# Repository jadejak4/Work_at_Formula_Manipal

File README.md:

# Work at Formula Manipal

Hi, hope this finds you well. This repository summarizes the majority of the technical work that was executed collaboratively by my teammates and me during my tenure at Formula Manipal.

## Projects at Formula Manipal

Broadly speaking, my projects at FM included:

- **Hardware & Firmware Design** of a Data Acquisition system for a Formula Student car.
- **Integrating a telemetry system** using XBee modules & displaying data using a GUI.
- **Designing & manufacturing a wiring harness**, compatible with the mechanical design and Engine Control Unit.
- **Designing, prototyping & manufacturing PCBs** for digital circuits used in the shutdown system for the car.

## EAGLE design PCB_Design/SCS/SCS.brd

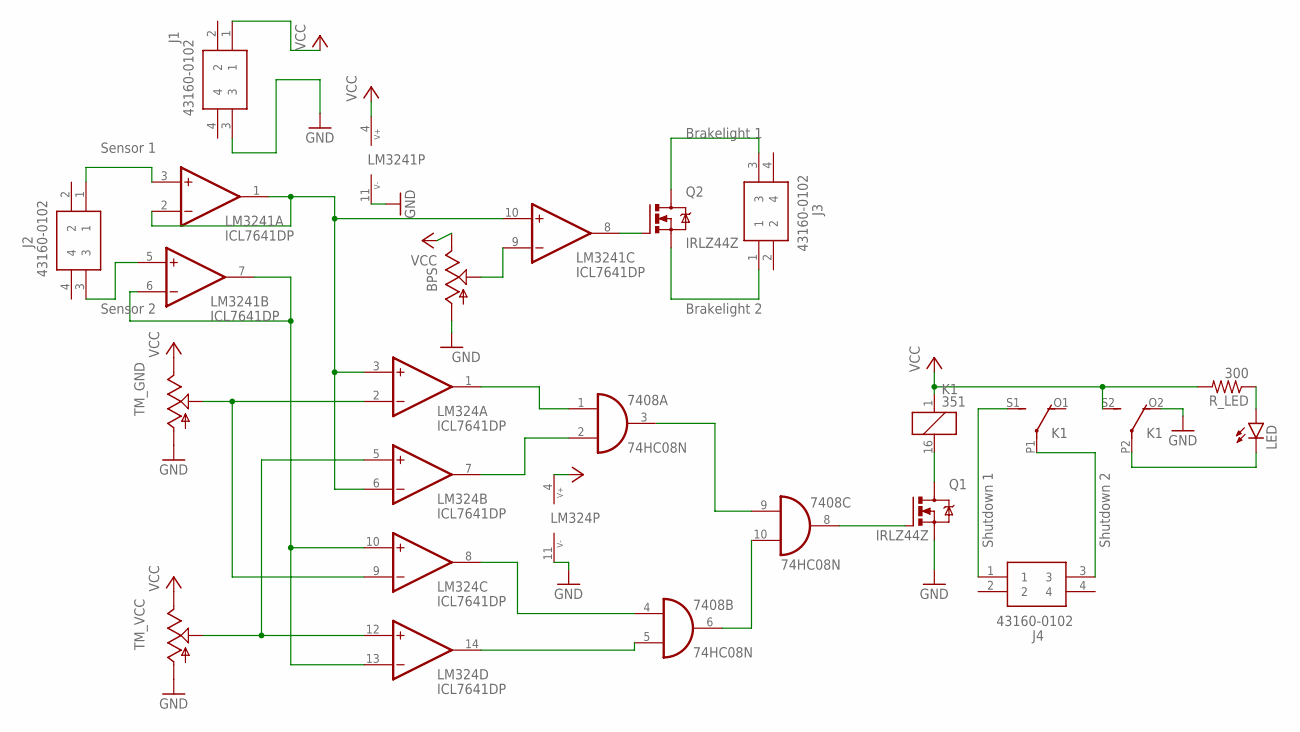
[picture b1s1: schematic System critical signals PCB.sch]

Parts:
7408: 74HC08N; DIL14
BPS: TRIM; 6MM
J1, J2, J3, J4: 43160-0102; 431600102
K1: 351
LED: LEDCHIP-LED0805; CHIP-LED0805
LM324, LM3241: ICL7641DP; DIL14
Q1, Q2: IRLZ44Z; TO220BH
R_LED: 300; M0805
TM_GND: TRIM; 6MM
TM_VCC: TRIM; 6MM

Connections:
GND: 7408.7 (GND), BPS.A, J1.3, K1.O2 (O), LM324.11 (V-), LM3241.11 (V-), Q1.S, TM_GND.A, TM_VCC.A
unnamed: 7408.4 (I0), LM324.8 (OUT)
unnamed: LM324.3 (+IN), LM324.6 (-IN), LM3241.1 (OUT), LM3241.2 (-IN), LM3241.10 (+IN)
unnamed: LM324.10 (+IN), LM324.13 (-IN), LM3241.6 (-IN), LM3241.7 (OUT)
unnamed: 7408.5 (I1), LM324.14 (OUT)
unnamed: 7408.1 (I0), LM324.1 (OUT)
unnamed: 7408.2 (I1), LM324.7 (OUT)
unnamed: 7408.3 (O), 7408.9 (I0)
unnamed: 7408.6 (O), 7408.10 (I1)
unnamed: 7408.8 (O), Q1.G
unnamed: K1.16 (2), Q1.D
unnamed: J4.1, K1.S1 (S)
unnamed: J4.3, K1.P1
unnamed: LED.A, R_LED.1
unnamed: BPS.S, LM3241.9 (-IN)
unnamed: LM3241.8 (OUT), Q2.G
unnamed: J3.3, Q2.D
unnamed: J3.1, Q2.S
unnamed: K1.P2, LED.C
unnamed: J2.1, LM3241.3 (+IN)
unnamed: J2.3, LM3241.5 (+IN)
unnamed: LM324.2 (-IN), LM324.9 (-IN), TM_GND.S
unnamed: LM324.5 (+IN), LM324.12 (+IN), TM_VCC.S
VCC: 7408.14 (VCC), BPS.E, J1.1, K1.1, K1.S2 (S), LM324.4 (V+), LM3241.4 (V+), R_LED.2, TM_GND.E, TM_VCC.E

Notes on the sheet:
Sensor 1
Sensor 2
Shutdown 1
Shutdown 2
Brakelight 1
Brakelight 2

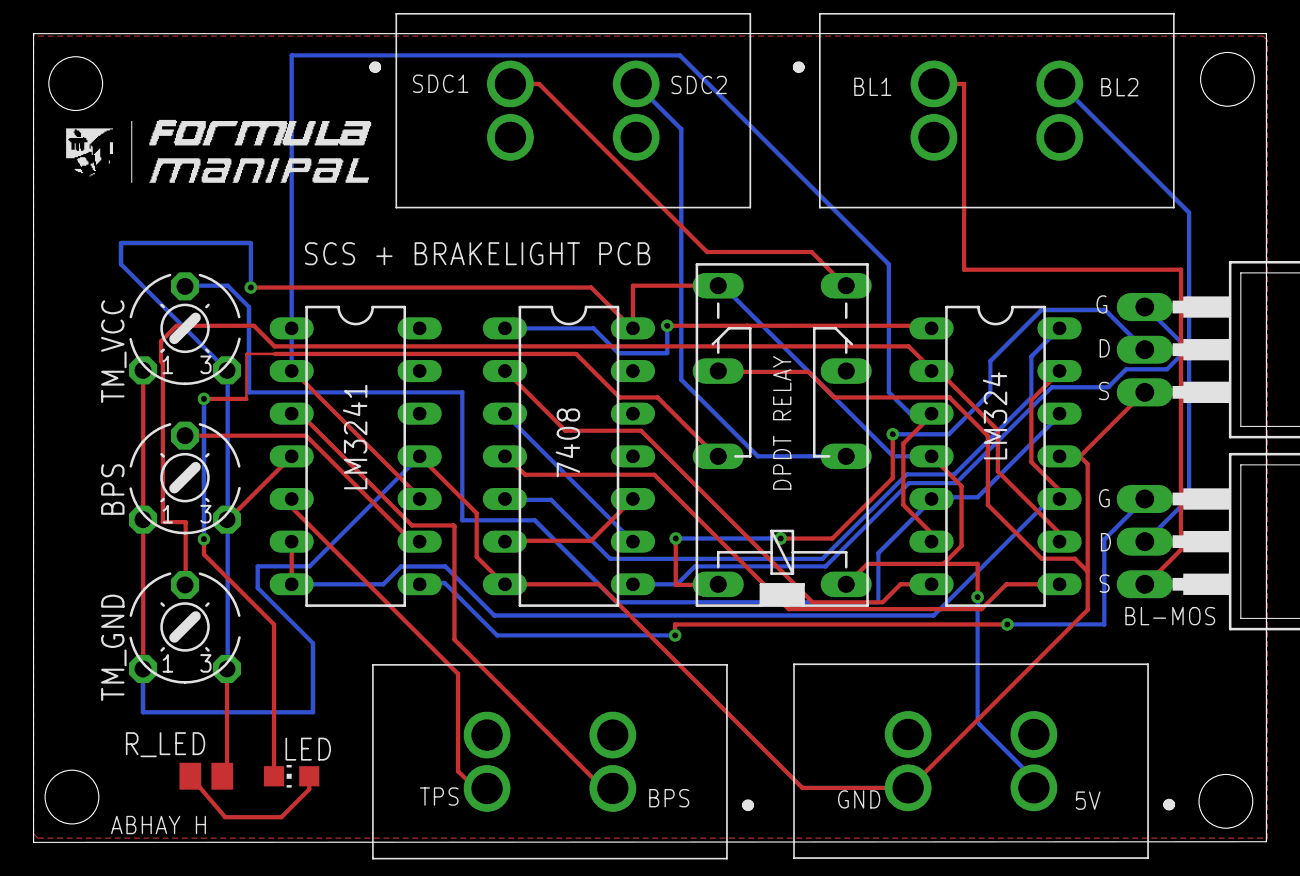
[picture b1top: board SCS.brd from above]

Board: 2 copper layers, 73.4 x 48.2 mm, 15 parts (0 on the bottom side), 24 nets.

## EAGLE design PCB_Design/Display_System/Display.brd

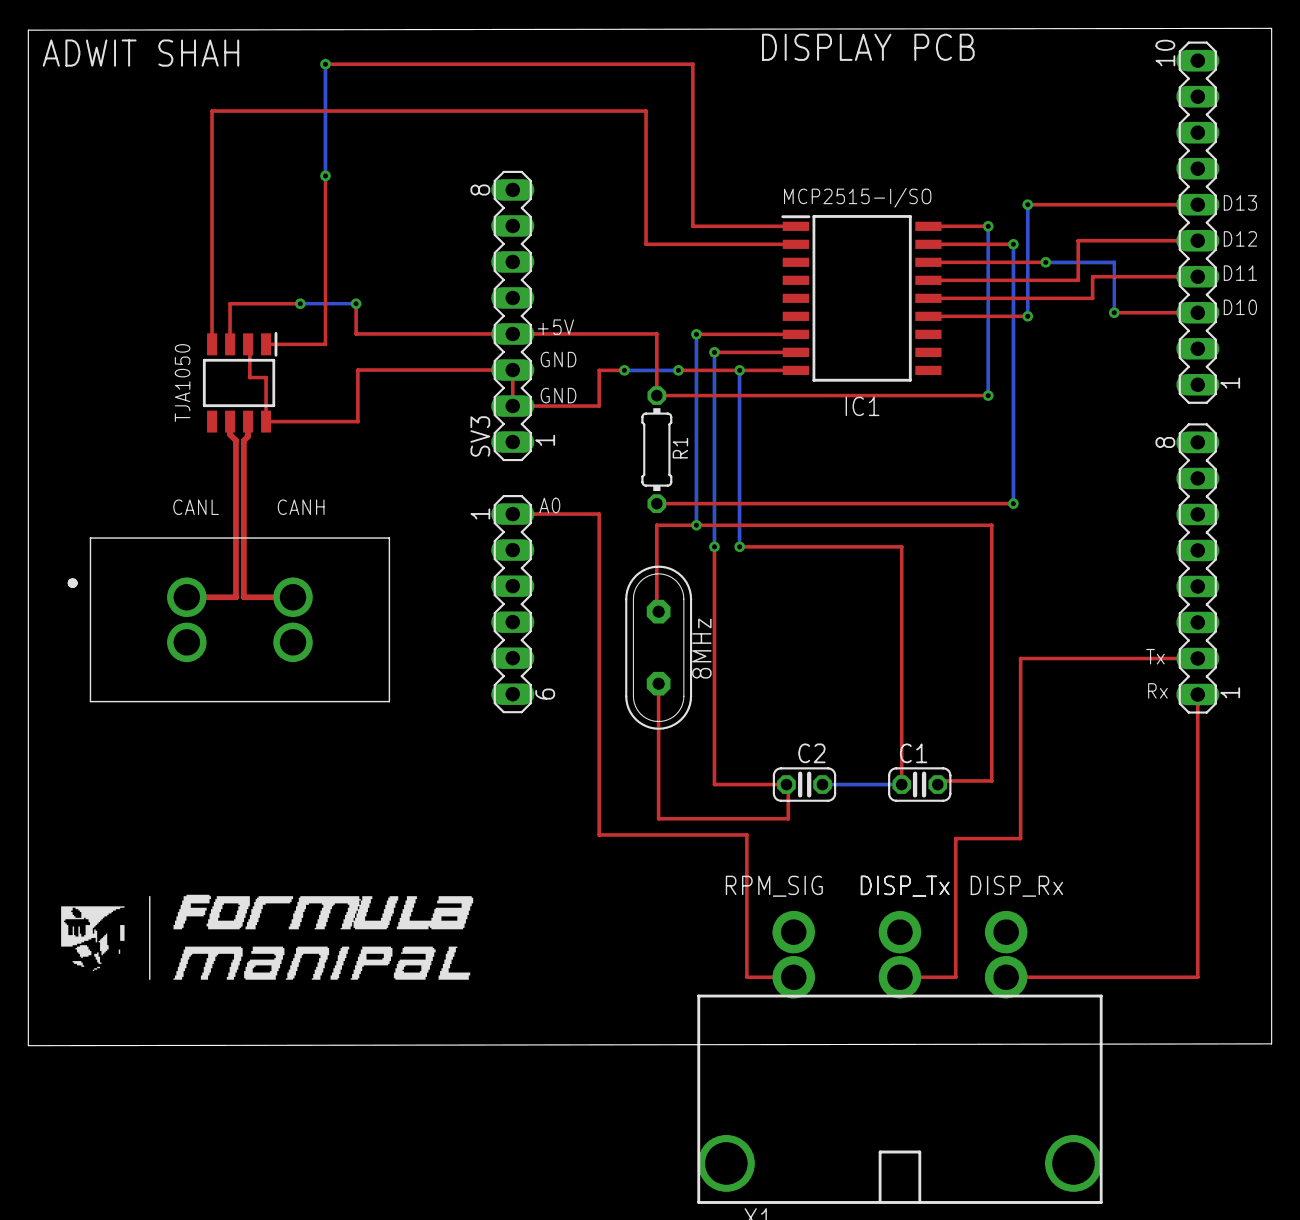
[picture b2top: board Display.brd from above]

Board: 2 copper layers, 87.7 x 71.7 mm, 12 parts (0 on the bottom side), 16 nets.

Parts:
C1, C2: 22pF; C025-024X044
DIFF_N: 43160-0102; 431600102
IC1: MCP2515-I_SO; SOIC127P1030X265-18N
IC2: TJA1050T_CM,118; SOIC127P600X175-8N
R1: 10K; 0204/7
SV1: MA06-1
SV2, SV3: MA08-1
SV4: MA10-1
X1: 43160-5303; 43160-XX03
Y2: 16MHz; QS

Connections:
DIFF1_N: C2.1, IC1.8, Y2.2
DIFF1_P: C1.1, IC1.7, Y2.1
DIFF_N: DIFF_N.1, IC2.6
DIFF_P: DIFF_N.3, IC2.7
GND: C1.2, C2.2, IC1.9, IC2.2, IC2.8, SV3.2, SV3.3
unnamed: IC1.15, SV4.5
unnamed: SV2.1, X1.3@1
unnamed: IC1.1, IC2.1
unnamed: IC1.2, IC2.4
unnamed: IC1.16, SV4.3
unnamed: IC1.14, SV4.4
unnamed: SV1.1, X1.1@1
unnamed: IC1.13, SV4.6
unnamed: IC1.17, R1.2
unnamed: SV2.2, X1.2@1
unnamed: IC1.18, IC2.3, R1.1, SV3.4

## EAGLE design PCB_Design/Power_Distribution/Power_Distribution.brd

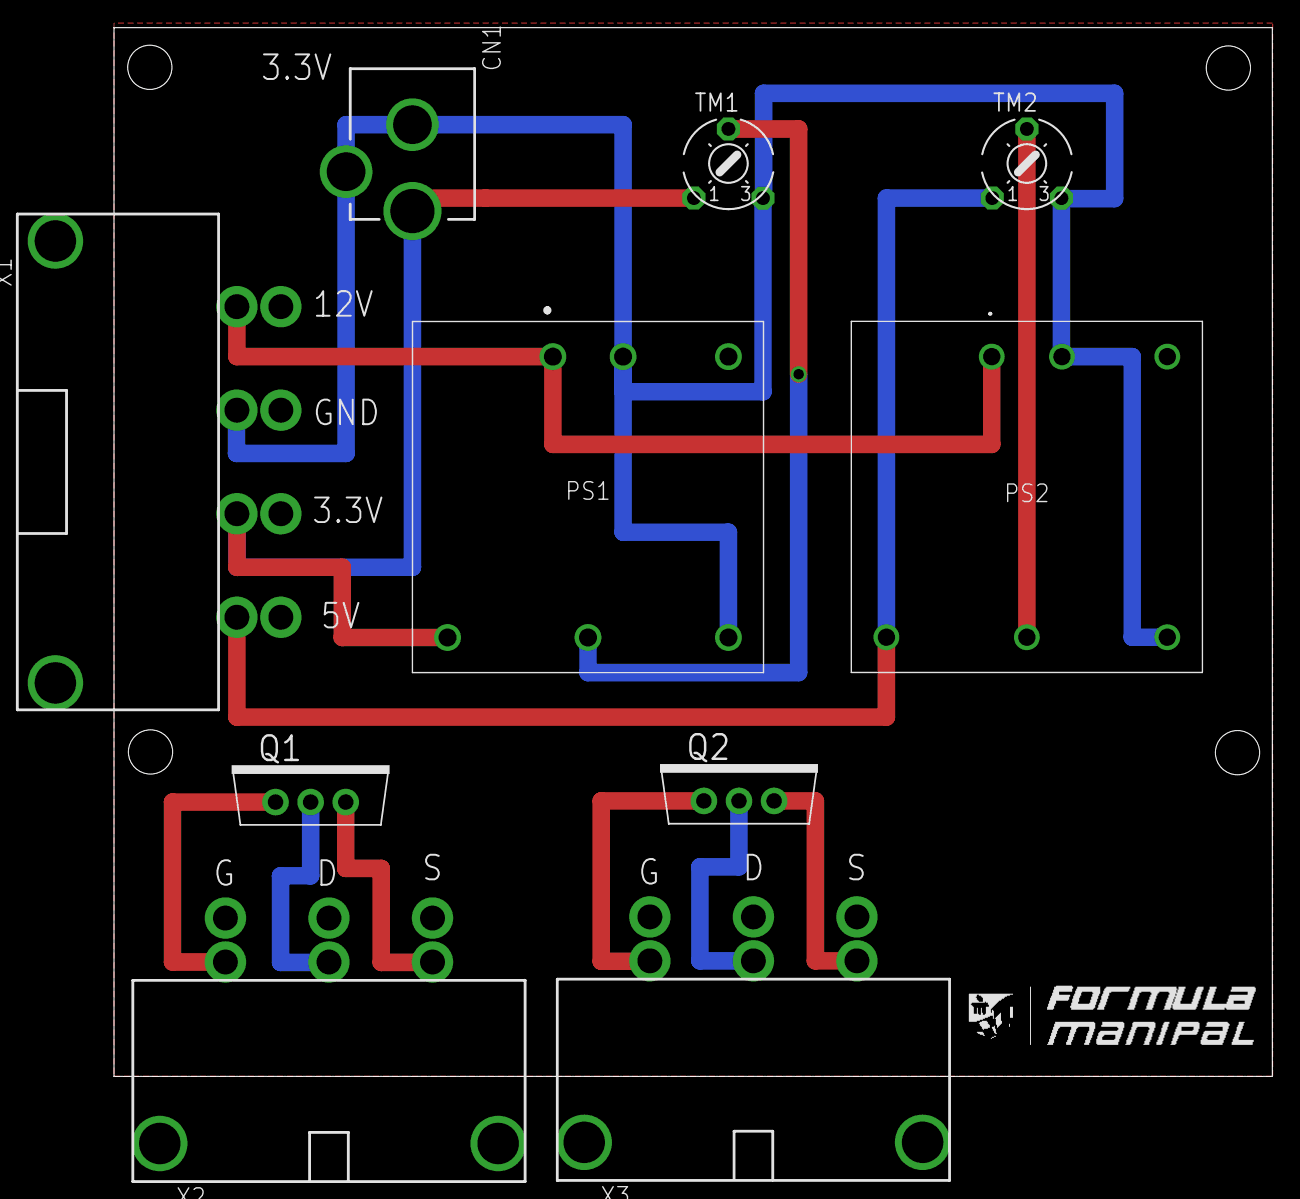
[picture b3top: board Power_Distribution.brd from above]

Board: 2 copper layers, 83.8 x 75.9 mm, 10 parts (0 on the bottom side), 12 nets.

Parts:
CN1: DCJACK_2MM_PTH
PS1: THL_15-2410WI; THL152410WI
PS2: THL_15-2411WI; THL152411WI
Q1, Q2: IRLZ44Z; TO220BH
TM1, TM2: 6MM
X1: 43160-5304; 43160-XX04
X2, X3: 43160-5303; 43160-XX03

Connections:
3.3V: CN1.PWR, PS1.3, TM1.A, X1.3@1
5V: PS2.3, TM2.A, X1.4@1
12VINPUT: PS1.1, PS2.1, X1.1@1
DRAIN1: Q1.D, X2.2@1
DRAIN2: Q2.D, X3.2@1
GATE1: Q1.G, X2.1@1
GATE2: Q2.G, X3.1@1
GND: CN1.GND, CN1.GNDBREAK, PS1.2, PS1.5, PS2.2, PS2.5, TM1.E, TM2.E, X1.2@1
unnamed: PS1.4, TM1.S
unnamed: PS2.4, TM2.S
SOURCE1: Q1.S, X2.3@1
SOURCE2: Q2.S, X3.3@1

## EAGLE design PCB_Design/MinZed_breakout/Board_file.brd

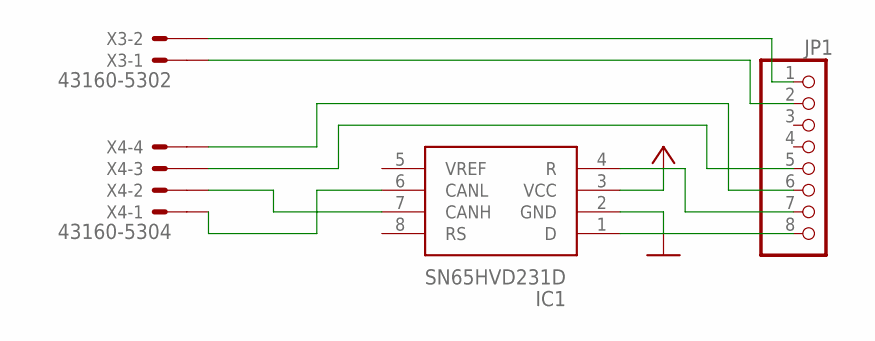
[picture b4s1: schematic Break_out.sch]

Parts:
IC1: SN65HVD231D; SOIC127P600X175-8N
JP1: PINHD-1X8BIG; 1X08-BIG
X3: 43160-5302; 43160-XX02
X4: 43160-5304; 43160-XX04

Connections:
GND: IC1.2 (GND)
unnamed: IC1.1 (D), JP1.8
unnamed: IC1.4 (R), JP1.7
unnamed: IC1.7 (CANH), X4.2@1
unnamed: IC1.6 (CANL), X4.1@1
unnamed: JP1.5, X4.3@1
unnamed: JP1.6, X4.4@1
unnamed: JP1.2, X3.1@1
unnamed: JP1.1, X3.2@1
VCC: IC1.3 (VCC)

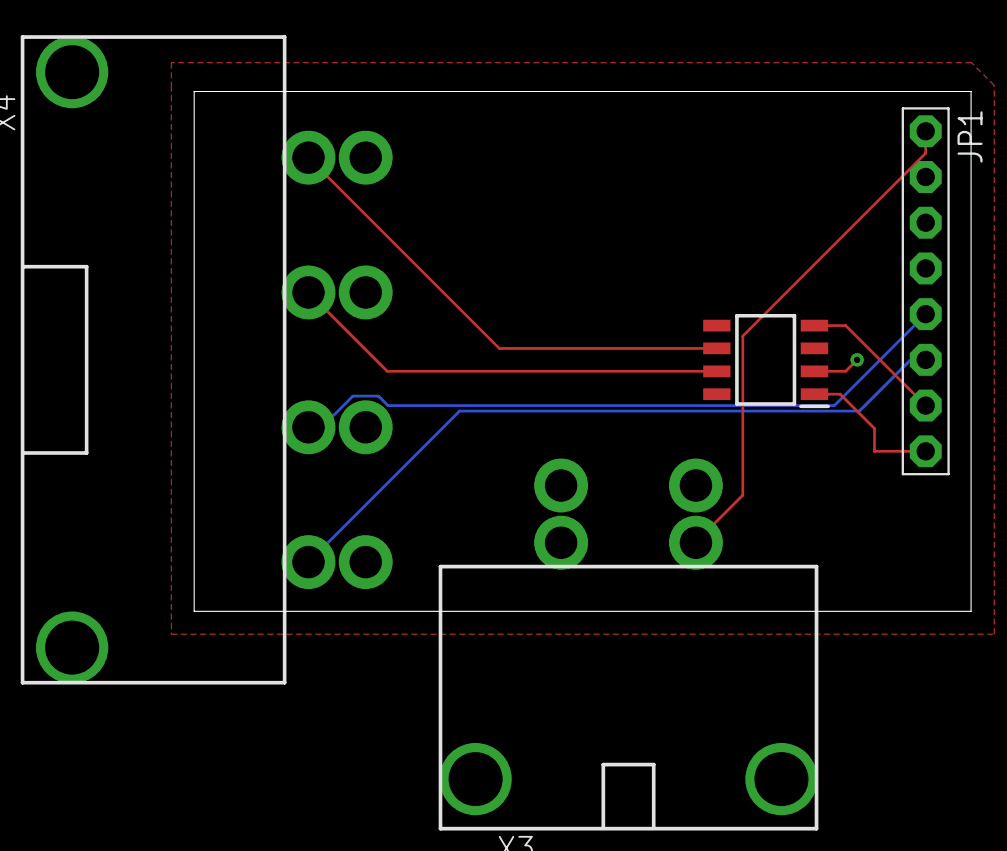
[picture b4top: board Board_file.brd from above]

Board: 2 copper layers, 43.2 x 28.9 mm, 4 parts (0 on the bottom side), 8 nets.

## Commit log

2023-06-03 Create MiniZed_Breakout
2023-06-03 Create Display_System
